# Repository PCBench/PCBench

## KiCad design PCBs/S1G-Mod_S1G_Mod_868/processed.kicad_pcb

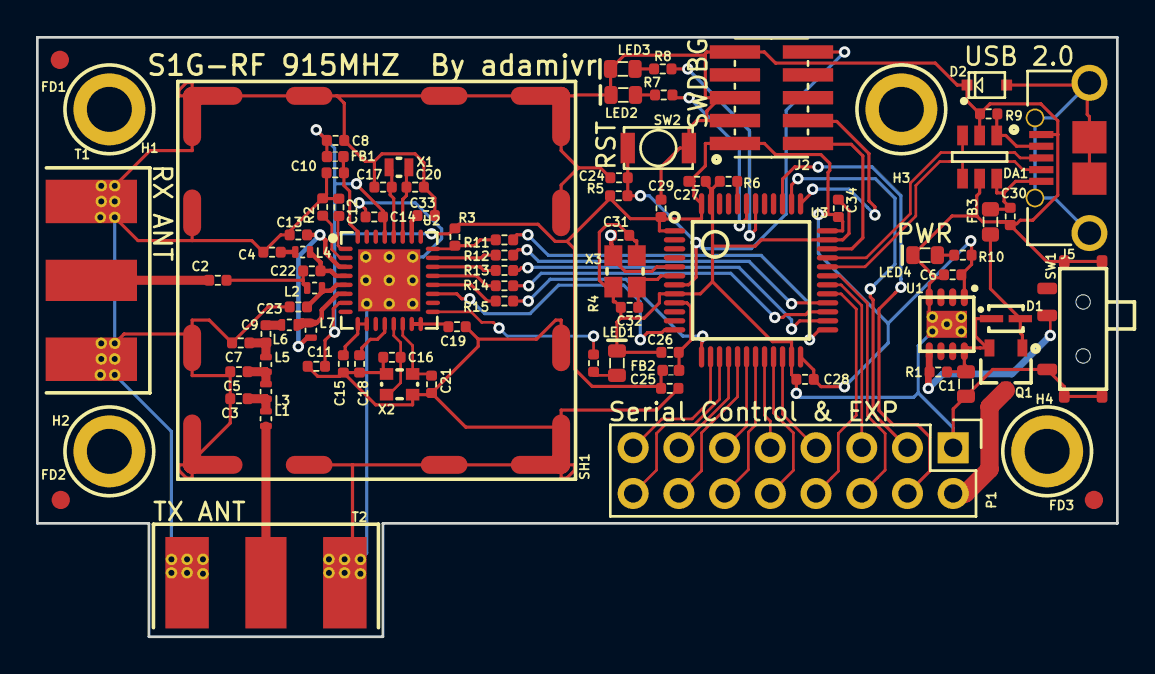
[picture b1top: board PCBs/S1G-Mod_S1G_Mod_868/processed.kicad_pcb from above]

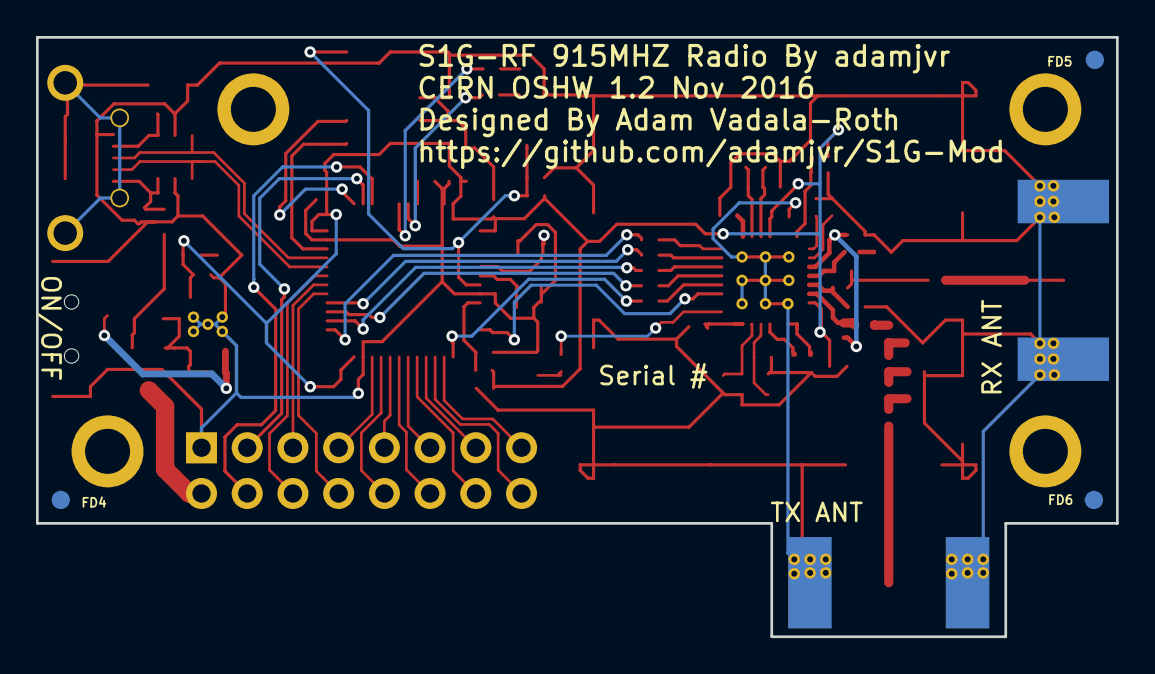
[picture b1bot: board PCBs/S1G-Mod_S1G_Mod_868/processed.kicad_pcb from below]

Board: 4 copper layers, 60.0 x 33.3 mm, 91 parts (3 on the bottom side), 73 nets.

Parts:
C1: CL10A106KQ8NNNC; C0603
C2: CBR04C560F1GAC; C0402
C3, C5: GJM1555C1H2R2WB01D; C0402
C4: GRM1555C1H101GA01D; C0402
C6, C8, C10, C11, C14, C24, C25, C26, C27, C28, C29, C30, C34: CL05B104JP5NNNC; C0402
C7: GJM1555C1H1R0BB01D; C0402
C9: CBR04C470F3GAC; C0402
C12, C13, C15, C19, C33: CL10B224JO8NNNC; C0402
C16, C21, C31, C32: GRM0225C1E8R0WA03L; C0402
C17, C20: CL05C090CB5NNNC; C0402
C18: GRM155R71H152KA01D; C0402
C22: GRM1555C2A2R7CA01D; C0402
C23: GRM1555C1E1R2BA01D; C0402
D1: BAT20JFILM
D2: RSB39VTE-17
DA1: ESDA6V1BC6
FB1, FB2: BLM15HG601SN1D
FB3: MI0603K300R-10
FD1, FD2, FD3, FD4, FD5, FD6: FIDUCIAL
H1, H2, H3, H4: M2.5_Hole; M2.5_HOLE
J2: 20021121-00010C4LF
J5: 0475890001-MicroUSBPort; 0475890001
L1, L2, L5: 0402CS-12NXJL; L0402
L3: 0402CS-24NXJL; L0402
L4: 0402CS-6N2XJL; L0402
L6: 0402CS-1N8XJL; L0402
L7: 0402CS-47NXJL; L0402
LED1, LED2: LTST-C193TBKT-5A; LED0603
LED3: LTST-C191KGKT; LED0603
LED4: LTST-C193KRKT-5A; LED0603
P1: 61301621121
Q1: DMG2307L-7
R1, R3, R6: RC1005F103CS; R0402
R2: ERA-2AEB363X; R0402
R4, R5, R7, R8, R10: RC1005F102CS; R0402
R9: RC1005J473CS; R0402
R11, R12, R13, R14, R15: TNPW0402100RBEED; R0402
SH1: 36103205
SW1: CUS-12TB
SW2: B3U-1000P
T1, T2: 732511150; 0732511150
U1: AP7361-33FGE-7
U2: ADF7023BCPZ
U3: STM32L052C8T6
X1: ABS05-32.768KHZ-9-T
X2: ABM11-140-26.000MHZ-T3
X3: ABM10-166-12.000MHZ-T3

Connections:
+3V3: C6.1, C8.2, C11.1, C14.2, C25.1, C27.1, C28.1, C29.1, C34.1, FB1.1, FB2.1, J2.1, R3.1, R5.1, R10.2, U1.1, U2.7, U2.29, U3.1, U3.24, U3.36, U3.48
/GPIO2: U2.19, U3.12
/MCU - STM32L052K8T6/GPIO_PA8: P1.8, U3.29
/MCU - STM32L052K8T6/GPIO_PA15: P1.3, U3.38
/MCU - STM32L052K8T6/GPIO_PB0: P1.11, U3.18
/MCU - STM32L052K8T6/GPIO_PB1: P1.12, U3.19
/MCU - STM32L052K8T6/GPIO_PB2: P1.9, U3.20
/MCU - STM32L052K8T6/GPIO_PB3: P1.4, U3.39
/MCU - STM32L052K8T6/GPIO_PB10: P1.10, U3.21
/MCU - STM32L052K8T6/GPIO_PB11: P1.7, U3.22
/MCU - STM32L052K8T6/MCU_IRQ: R15.2, U3.13
/MCU - STM32L052K8T6/NRST: C24.1, J2.10, R5.2, SW2.2, U3.7
/MCU - STM32L052K8T6/SPI2_MISO: P1.13, U3.16
/MCU - STM32L052K8T6/SPI2_MOSI: P1.14, U3.17
/MCU - STM32L052K8T6/SPI2_NSS: P1.15, U3.14
/MCU - STM32L052K8T6/SPI2_SCLK: P1.16, U3.15
/MCU - STM32L052K8T6/SPI_CS: R11.2, U3.25
/MCU - STM32L052K8T6/SPI_MISO: R14.2, U3.27
/MCU - STM32L052K8T6/SPI_MOSI: R12.2, U3.28
/MCU - STM32L052K8T6/SPI_SCLK: R13.2, U3.26
/MCU - STM32L052K8T6/SWCLK: J2.4, U3.37
/MCU - STM32L052K8T6/SWDIO: J2.2, U3.34
/MCU - STM32L052K8T6/USART1_RX: P1.6, U3.31
/MCU - STM32L052K8T6/USART1_TX: P1.5, U3.30
/MCU - STM32L052K8T6/USB_DM: DA1.4, J5.2, U3.32
/MCU - STM32L052K8T6/USB_DP: DA1.3, J5.3, U3.33
/MCU_IRQ: R15.1, U2.20
/ON_OFF: R1.1, SW1.2, U1.5
/PSU_IN: P1.2, Q1.3
/SPI_CS: R3.2, R11.1, U2.24
/SPI_MISO: R14.1, U2.21
/SPI_MOSI: R12.1, U2.23
/SPI_SCLK: R13.1, U2.22
/VBUS: D1.1, FB3.1, Q1.1
/VIN: C1.1, D1.2, Q1.2, R1.2, U1.8
/VREF: C10.2, FB1.2, U2.32
GND: C1.2, C3.2, C4.1, C5.2, C6.2, C7.2, C8.1, C10.1, C11.2, C12.1, C13.1, C14.1, C15.2, C16.2, C17.1, C18.2, C19.2, C20.2, C21.2, C23.1, C24.2, C25.2, C26.2, C27.2, C28.2, C29.2, C30.1, C31.2, C32.2, C33.2, C34.2, D2.2, DA1.2, DA1.5, J2.3, J2.5, J2.9, J5.5, LED1.2, LED2.2, LED3.2, LED4.2, P1.1, R2.1, R6.1, R9.2, SH1.1, SW1.1, SW1.4, SW2.1, T1.2, T2.2, U1.4, U1.9, U2.33, U3.8, U3.23, U3.35, U3.47, X2.2, X2.4, X3.2, X3.4
unnamed: C2.1, T1.1
unnamed: C2.2, C22.1, L2.1
unnamed: C3.1, L1.2, L3.1
unnamed: C4.2, L4.1
unnamed: C5.1, L3.2, L5.1
unnamed: C7.1, C9.1, L5.2
unnamed: C9.2, L6.1
unnamed: C12.2, U2.1
unnamed: C13.2, L7.1, U2.3
unnamed: C15.1, U2.9, U2.10
unnamed: C16.1, U2.13, X2.1
unnamed: C17.2, U2.28, X1.1
unnamed: C18.1, U2.12
unnamed: C19.1, U2.15, U2.16
unnamed: C20.1, U2.27, X1.2
unnamed: C21.1, U2.14, X2.3
unnamed: C22.2, L4.2, U2.4
unnamed: C23.2, L2.2, U2.5
unnamed: C26.1, FB2.2, U3.9
unnamed: C30.2, DA1.6, FB3.2, J5.1
unnamed: C31.1, U3.5, X3.1
unnamed: C32.1, U3.6, X3.3
unnamed: C33.1, U2.26
unnamed: D2.1, J5.6, J5.7, J5.8, J5.9, J5.10, J5.11
unnamed: DA1.1, J5.4, R9.1
unnamed: L1.1, T2.1
unnamed: L6.2, L7.2, U2.6
unnamed: LED1.1, R4.2
unnamed: LED2.1, R7.1
unnamed: LED3.1, R8.1
unnamed: LED4.1, R10.1
unnamed: R2.2, U2.2
unnamed: R4.1, U2.17
unnamed: R6.2, U3.44
unnamed: R7.2, U3.43
unnamed: R8.2, U3.42

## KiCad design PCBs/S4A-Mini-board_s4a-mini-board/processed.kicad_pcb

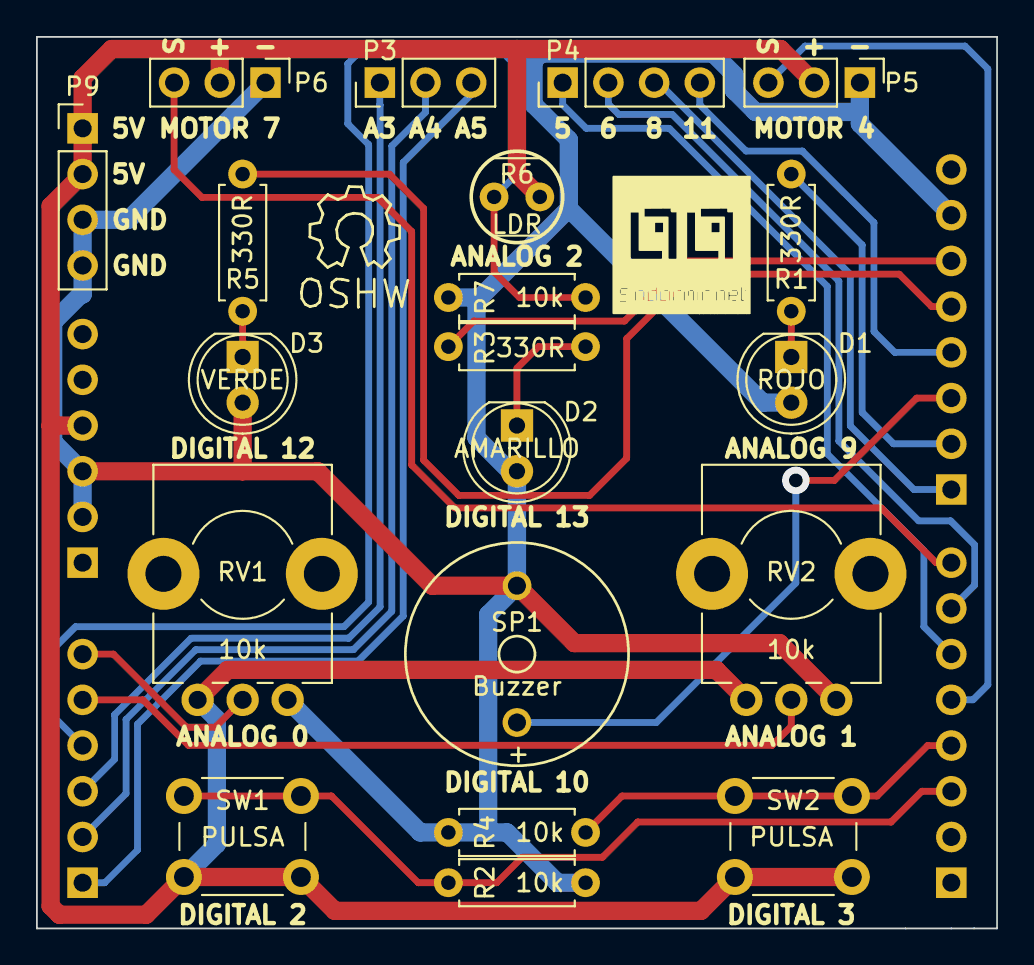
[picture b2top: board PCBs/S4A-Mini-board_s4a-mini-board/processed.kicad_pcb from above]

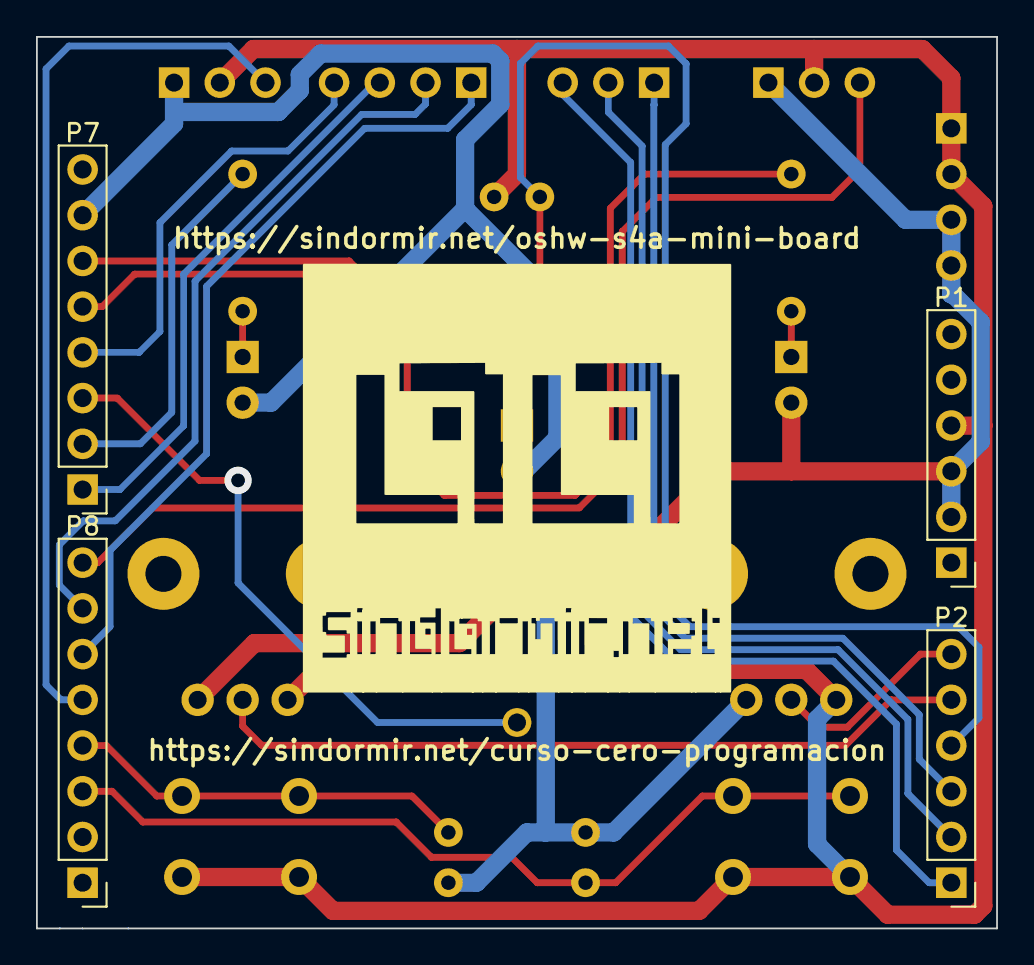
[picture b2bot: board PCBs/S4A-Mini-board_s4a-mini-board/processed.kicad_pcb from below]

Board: 2 copper layers, 53.3 x 49.5 mm, 25 parts (4 on the bottom side), 23 nets.

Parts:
D1: ROJO; LED_D5.0mm
D2: AMARILLO; LED_D5.0mm
D3: VERDE; LED_D5.0mm
P1: Arduino Power header; Pin_Header_Straight_1x06_Pitch2.54mm
P2: Arduino Analog header; Pin_Header_Straight_1x06_Pitch2.54mm
P3: Analog pin; Socket_Strip_Straight_1x03_Pitch2.54mm
P4: Digital pin; Socket_Strip_Straight_1x04_Pitch2.54mm
P5: Servo 1; Pin_Header_Straight_1x03_Pitch2.54mm
P6: Servo 2; Pin_Header_Straight_1x03_Pitch2.54mm
P7: Arduino Digital H header; Pin_Header_Straight_1x08_Pitch2.54mm
P8: Arduino Digital L header; Pin_Header_Straight_1x08_Pitch2.54mm
P9: Power; Socket_Strip_Straight_1x04_Pitch2.54mm
R1, R3, R5: 330R; R_Axial_DIN0207_L6.3mm_D2.5mm_P7.62mm_Horizontal
R2, R4, R7: 10k; R_Axial_DIN0207_L6.3mm_D2.5mm_P7.62mm_Horizontal
R6: LDR; Resistor_LDR_4.9x4.2_RM2.54
RV1, RV2: 10k; Potentiometer_Alps_RK09K_Horizontal
SP1: Buzzer; MagneticBuzzer_ProSignal_ABI-009-RC
SW1, SW2: PULSA; SW_PUSH_6mm_h5mm
Symbol_OSHW-Logo_SilkScreen: VAL**; Symbol_OSHW-Logo_SilkScreen

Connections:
+5V: P1.4, P5.2, P6.2, P9.1, P9.2, R6.1, RV1.3, RV2.3, SW1.1, SW2.1
GND: D1.2, D2.2, D3.2, P1.2, P1.3, P5.1, P6.1, P7.7, P9.3, P9.4, R2.2, R4.2, R7.2, RV1.1, RV2.1, SP1.1
unnamed: D1.1, R1.1
unnamed: D2.1, R3.1
unnamed: D3.1, R5.1
PINA0: P2.6, RV1.2
PINA1: P2.5, RV2.2
PINA2: P2.4, R6.2, R7.1
PINA3: P2.3, P3.1
PINA4: P2.2, P3.2
PINA5: P2.1, P3.3
PIND2: P8.3, R2.1, SW1.2
PIND3: P8.4, R4.1, SW2.2
PIND4: P5.3, P8.5
PIND5: P4.1, P8.6
PIND6: P4.2, P8.7
PIND7: P6.3, P8.8
PIND8: P4.3, P7.1
PIND9: P7.2, R1.2
PIND10: P7.3, SP1.2
PIND11: P4.4, P7.4
PIND12: P7.5, R5.2
PIND13: P7.6, R3.2

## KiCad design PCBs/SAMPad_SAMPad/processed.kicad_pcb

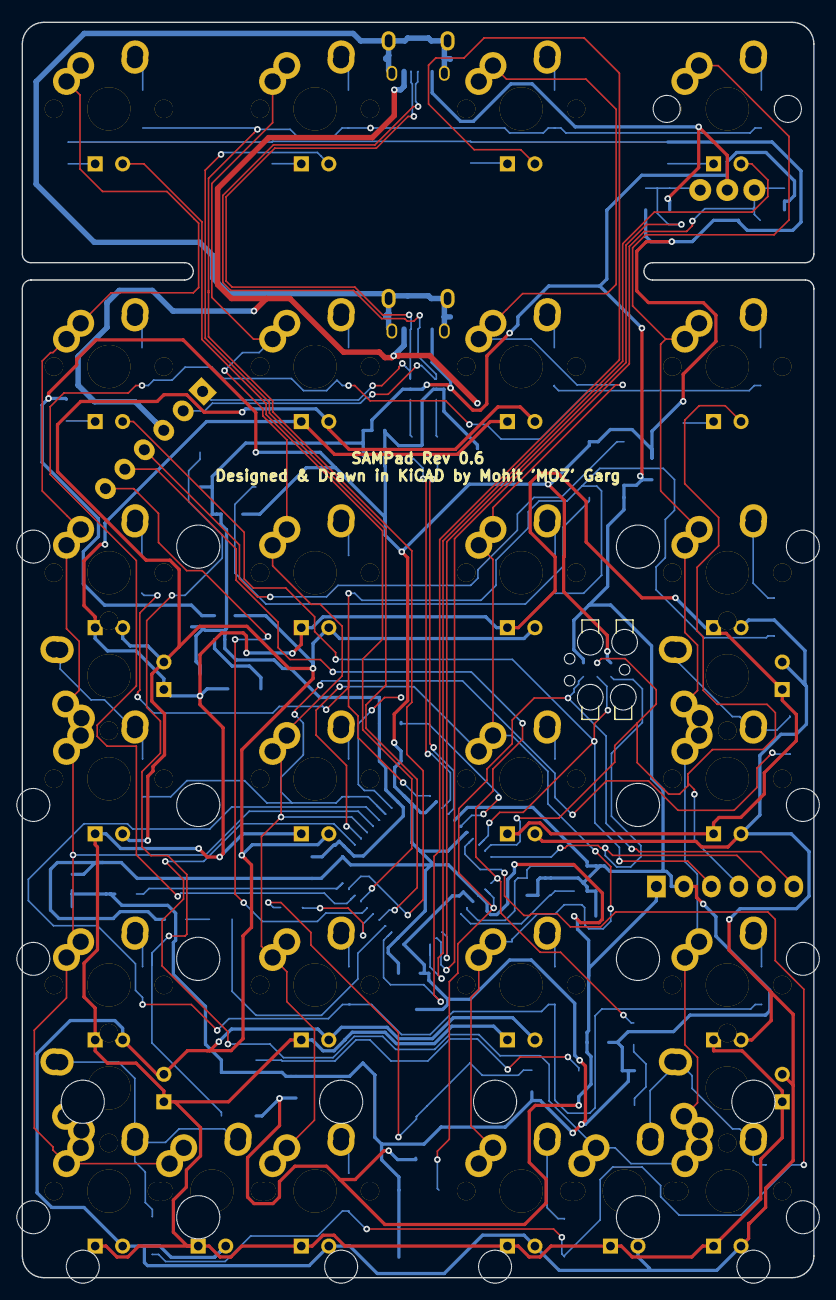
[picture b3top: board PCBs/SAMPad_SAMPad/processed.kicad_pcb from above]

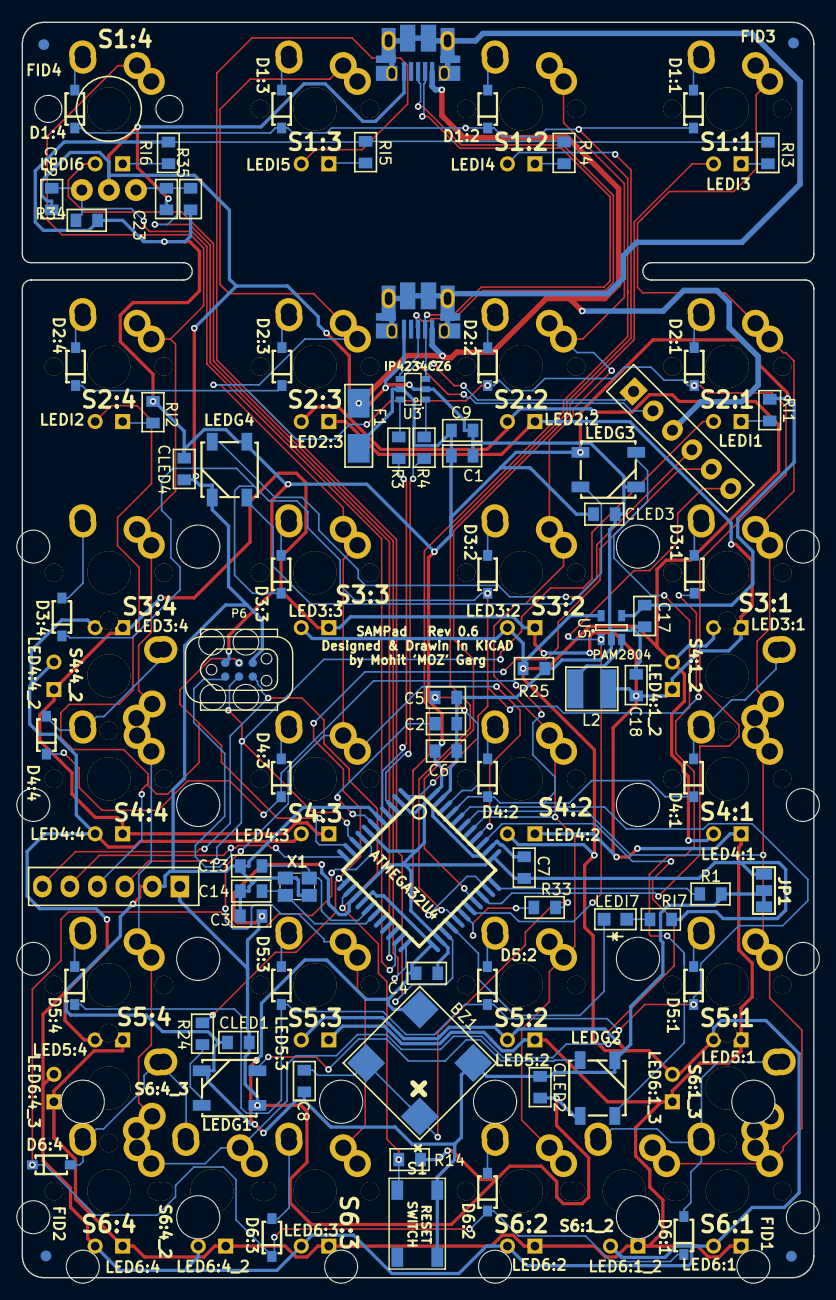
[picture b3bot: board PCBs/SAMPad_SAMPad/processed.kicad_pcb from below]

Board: 2 copper layers, 73.2 x 116.0 mm, 150 parts (83 on the bottom side), 79 nets.

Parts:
BZ1: BUZZER; BUZZER_SMT
C1, C2, C22, C23: 1uF; SMD_0805
C3, C4, C5, C6, C7, C8: 0.1uF; SMD_0805
C9, C17, C18: 10uF; SMD_0805
C13, C14: 8pF; SMD_0805
CLED1, CLED2, CLED3, CLED4: 0.1 uF; SMD_0805
D1:1, D1:2, D1:3, D1:4, D2:1, D2:2, D2:3, D2:4, D3:1, D3:2, D3:3, D3:4, D4:1, D4:2, D4:3, D4:4, D5:1, D5:2, D5:3, D5:4, D6:1, D6:2, D6:3, D6:4: DIODE; SOD123-DIODE
F1: PTC FUSE; Fuse_SMD1206
FID1, FID2, FID3, FID4: MISC; FID
HOLE1: MISC; FID
JP1: JUMPER; JUMPER_SMD_3
L2: 4.7uH; Inductor_Bourn_4mmx4mm
LED2:2, LED2:3, LED3:1, LED3:2, LED3:3, LED3:4, LED4:1, LED4:1_2, LED4:2, LED4:3, LED4:4, LED4:4_2, LED5:1, LED5:2, LED5:3, LED5:4, LED6:1, LED6:1_2, LED6:1_3, LED6:2, LED6:3, LED6:4, LED6:4_2, LED6:4_3: LED; INSW_LEDS_REG
LEDG1, LEDG2, LEDG3, LEDG4: WS2812B
LEDI1, LEDI2, LEDI3, LEDI4, LEDI5, LEDI6: LED; INSW_LEDS_REG
LEDI7: LED; LED_0805
P1, P1_2: USB_CONN; USB_Micro-B
P4, P5: CONN_6; Pin_Header_1x06
P6: ISP6; TC2030_BIG
R1, R34, R35: 10k; SMD_0805
R3, R4: 22; SMD_0805
R14: 100k; SMD_0805
R24: 330; SMD_0805
R25: RLED; SMD_0805
R33: 100; SMD_0805
RI1, RI2, RI3, RI4, RI5, RI6, RI7: 470; SMD_0805
S1: TAC_SWITCH; TACT_5.2x5.2
S1:1, S1:2, S1:3, S1:4, S2:1, S2:2, S2:3, S2:4, S3:1, S3:2, S3:3, S3:4, S4:1, S4:1_2, S4:2, S4:3, S4:4, S4:4_2, S5:1, S5:2, S5:3, S5:4, S6:1, S6:1_2, S6:1_3, S6:2, S6:3, S6:4, S6:4_2, S6:4_3: SW; MXALPS2
S2: ENCODER; ENCODER_12MM
STAB1, STAB2, STAB3, STAB4, STAB5, STAB6: MISC; MX_200
U1: ATMEGA32U4; TQFP44
U3: IP4234CZ6; SOT457
U5: PAM2804; SOT-23-5
X1: CRYSTAL; NX3225SA

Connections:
+5V: C1.1, C3.1, C4.1, C6.1, C7.1, C9.1, C17.1, CLED1.2, CLED2.2, CLED3.1, CLED4.1, F1.2, JP1.1, LEDG1.1, LEDG2.1, LEDG3.1, LEDG4.1, P5.1, P6.2, R14.2, R34.2, R35.1, RI1.2, RI2.2, RI3.2, RI4.2, RI5.2, RI6.2, RI7.2, U1.2, U1.7, U1.14, U1.24, U1.34, U1.44, U3.5, U5.4
/ledmatrix/LEDAN: C18.1, L2.2, LED2:2.1, LED2:3.1, LED3:1.1, LED3:2.1, LED3:3.1, LED3:4.1, LED4:1.1, LED4:1_2.1, LED4:2.1, LED4:3.1, LED4:4.1, LED4:4_2.1, LED5:1.1, LED5:2.1, LED5:3.1, LED5:4.1, LED6:1.1, LED6:1_2.1, LED6:1_3.1, LED6:2.1, LED6:3.1, LED6:4.1, LED6:4_2.1, LED6:4_3.1
/ledmatrix/LEDCATH: LED2:2.2, LED2:3.2, LED3:1.2, LED3:2.2, LED3:3.2, LED3:4.2, LED4:1.2, LED4:1_2.2, LED4:2.2, LED4:3.2, LED4:4.2, LED4:4_2.2, LED5:1.2, LED5:2.2, LED5:3.2, LED5:4.2, LED6:1.2, LED6:1_2.2, LED6:1_3.2, LED6:2.2, LED6:3.2, LED6:4.2, LED6:4_2.2, LED6:4_3.2, R25.2, U5.5
/ledmatrix/LEDI1: LEDI1.2, P5.3, P6.3, U1.9
/ledmatrix/LEDI2: LEDI2.2, P5.4, P6.4, U1.10
/ledmatrix/LEDI3: LEDI3.2, U1.30
/ledmatrix/LEDI4: LEDI4.2, U1.27
/ledmatrix/LEDI5: LEDI5.2, U1.25
/ledmatrix/LEDI6: LEDI6.2, U1.22
/ledmatrix/LEDI7: LEDI7.2, U1.26
/ledmatrix/RGBDIN: P4.5, R24.2, U1.12
/ledmatrix/RGBDOUT: LEDG4.2, P4.4
/mcu/BUZZER: R33.1, U1.28
/mcu/COL1: S1:1.1, S2:1.1, S3:1.1, S4:1.1, S4:1_2.1, S5:1.1, S6:1.1, S6:1_2.1, S6:1_3.1, U1.39
/mcu/COL2: S1:2.1, S2:2.1, S3:2.1, S4:2.1, S5:2.1, S6:2.1, U1.38
/mcu/COL3: S1:3.1, S2:3.1, S3:3.1, S4:3.1, S5:3.1, S6:3.1, U1.37
/mcu/COL4: S1:4.1, S2:4.1, S3:4.1, S4:4.1, S4:4_2.1, S5:4.1, S6:4.1, S6:4_2.1, S6:4_3.1, U1.36
/mcu/D+: P1.3, P1_2.3, P4.2, U3.4
/mcu/D-: P1.2, P1_2.2, P4.1, U3.3
/mcu/ENCA: C22.1, R34.1, S2.1, U1.21
/mcu/ENCB: C23.1, R35.2, S2.3, U1.20
/mcu/HWBE: R1.2, U1.33
/mcu/LEDBL: P4.6, U1.29, U5.1
/mcu/MCURST: P5.6, P6.5, R14.1, S1.2, U1.13
/mcu/MISO: P5.5, P6.1, U1.11
/mcu/ROW1: D1:1.2, D1:2.2, D1:3.2, D1:4.2, U1.32
/mcu/ROW2: D2:1.2, D2:2.2, D2:3.2, D2:4.2, U1.31
/mcu/ROW3: D3:1.2, D3:2.2, D3:3.2, D3:4.2, U1.1
/mcu/ROW4: D4:1.2, D4:2.2, D4:3.2, D4:4.2, U1.41
/mcu/ROW5: D5:1.2, D5:2.2, D5:3.2, D5:4.2, U1.40
/mcu/ROW6: D6:1.2, D6:2.2, D6:3.2, D6:4.2, U1.8
/mcu/SHDGND: P1.6, P1_2.6
/mcu/USB_D+: R3.2, U1.4
/mcu/USB_D-: R4.2, U1.3
/mcu/VUSB: F1.1, P1.1, P1_2.1, P4.3
/mcu/XTAL1: C14.1, U1.17, X1.3
/mcu/XTAL2: C13.1, U1.16, X1.1
unnamed: BZ1.1, C8.2, R33.2
unnamed: C2.1, U1.6
unnamed: C5.1, U1.42
unnamed: D1:1.1, S1:1.2
unnamed: D1:2.1, S1:2.2
unnamed: D1:3.1, S1:3.2
unnamed: D1:4.1, S1:4.2
unnamed: D2:1.1, S2:1.2
unnamed: D2:2.1, S2:2.2
unnamed: D2:3.1, S2:3.2
unnamed: D2:4.1, S2:4.2
unnamed: D3:1.1, S3:1.2
unnamed: D3:2.1, S3:2.2
unnamed: D3:3.1, S3:3.2
unnamed: D3:4.1, S3:4.2
unnamed: D4:1.1, S4:1.2, S4:1_2.2
unnamed: D4:2.1, S4:2.2
unnamed: D4:3.1, S4:3.2
unnamed: D4:4.1, S4:4.2, S4:4_2.2
unnamed: D5:1.1, S5:1.2
unnamed: D5:2.1, S5:2.2
unnamed: D5:3.1, S5:3.2
unnamed: D5:4.1, S5:4.2
unnamed: D6:1.1, S6:1.2, S6:1_2.2, S6:1_3.2
unnamed: D6:2.1, S6:2.2
unnamed: D6:3.1, S6:3.2
unnamed: D6:4.1, S6:4.2, S6:4_2.2, S6:4_3.2
unnamed: L2.1, U5.3
unnamed: LEDG1.2, LEDG2.4
unnamed: LEDG1.4, R24.1
unnamed: LEDG2.2, LEDG3.4
unnamed: LEDG3.2, LEDG4.4
unnamed: LEDI1.1, RI1.1
unnamed: LEDI2.1, RI2.1
unnamed: LEDI3.1, RI3.1
unnamed: LEDI4.1, RI4.1
unnamed: LEDI5.1, RI5.1
unnamed: LEDI6.1, RI6.1
unnamed: LEDI7.1, RI7.1
unnamed: R3.1, U3.6
unnamed: R4.1, U3.1
VSS: BZ1.2, C1.2, C2.2, C3.2, C4.2, C5.2, C6.2, C7.2, C8.1, C9.2, C13.2, C14.2, C17.2, C18.2, C22.2, C23.2, CLED1.1, CLED2.1, CLED3.2, CLED4.2, JP1.2, JP1.3, LEDG1.3, LEDG2.3, LEDG3.3, LEDG4.3, P1.5, P1_2.5, P5.2, P6.6, R1.1, R25.1, S1.3, S1.4, S2.2, U1.5, U1.15, U1.23, U1.35, U1.43, U3.2, U5.2, X1.2, X1.4

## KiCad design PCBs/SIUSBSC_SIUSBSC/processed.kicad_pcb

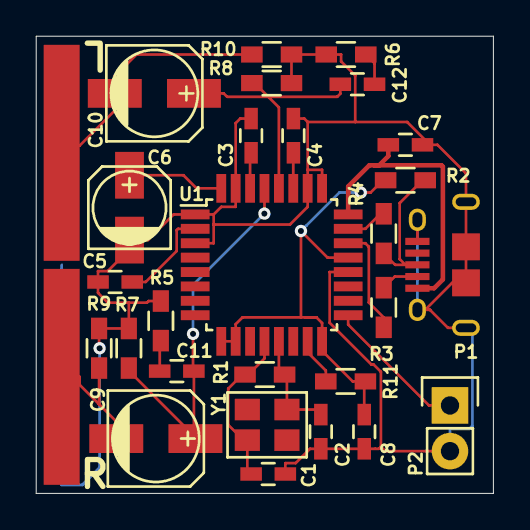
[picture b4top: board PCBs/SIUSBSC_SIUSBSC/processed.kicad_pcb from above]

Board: 2 copper layers, 25.4 x 25.4 mm, 30 parts (1 on the bottom side), 21 nets.

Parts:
C1, C2: 18pF; C_0603_HandSoldering
C3, C4, C5, C7, C8: 1uF; C_0603_HandSoldering
C6: 10uF; c_elec_4x5.3
C9, C10: 100uF; c_elec_5x5.3
C11, C12: 0.022uF; C_0603_HandSoldering
P1: USB_MICRO_B; CONN_USB_MICRO_B_FCI_10118194
P2: I2S; Pin_Header_Straight_1x02
P3: RIGHT; PAD_12.00x2.00mm
P4: LEFT; PAD_12.00x2.00mm
P5: GND; PAD_24.00x2.00mm
R1: 1M; R_0603_HandSoldering
R2, R11: 1K5; R_0603_HandSoldering
R3, R4: 22R; R_0603_HandSoldering
R5, R6: 16R; R_0603_HandSoldering
R7, R8, R9, R10: 3K3; R_0603_HandSoldering
U1: PCM2706; TQFP-32_7x7mm_Pitch0.8mm
Y1: 12MHz; XTAL_SMD_3225

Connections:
/D+: R4.2, U1.23
/D-: R3.2, U1.22
/DOUT: P2.1, U1.17
/DT: R11.1, U1.15
/FOUTL: C10.2, P4.1, R10.1
/FOUTR: C9.2, P3.1, R9.1
/USB_D+: P1.3, R2.2, R4.1
/USB_D-: P1.2, R3.1
/VBUS: C7.2, P1.1, U1.24
/VCCL: C4.1, U1.27
/VCCP: C5.2, U1.2
/VCCR: C3.1, U1.30
/VCOM: C6.1, U1.32
/VOUTL: C10.1, C12.1, R8.1, U1.28
/VOUTR: C9.1, C11.1, R7.1, U1.29
/XTI: C1.1, R1.2, U1.12, Y1.1
/XTO: C2.1, R1.1, U1.13, Y1.3
GND: C1.2, C2.2, C3.2, C4.2, C5.1, C6.2, C7.1, C8.2, P1.5, P1.6, P2.2, P5.1, R5.2, R6.2, R7.2, R8.2, R9.2, R10.2, U1.1, U1.3, U1.20, U1.25, U1.26, U1.31
unnamed: C11.2, R5.1
unnamed: C12.2, R6.1
VDD: C8.1, R2.1, R11.2, U1.9, U1.10, U1.16, U1.21

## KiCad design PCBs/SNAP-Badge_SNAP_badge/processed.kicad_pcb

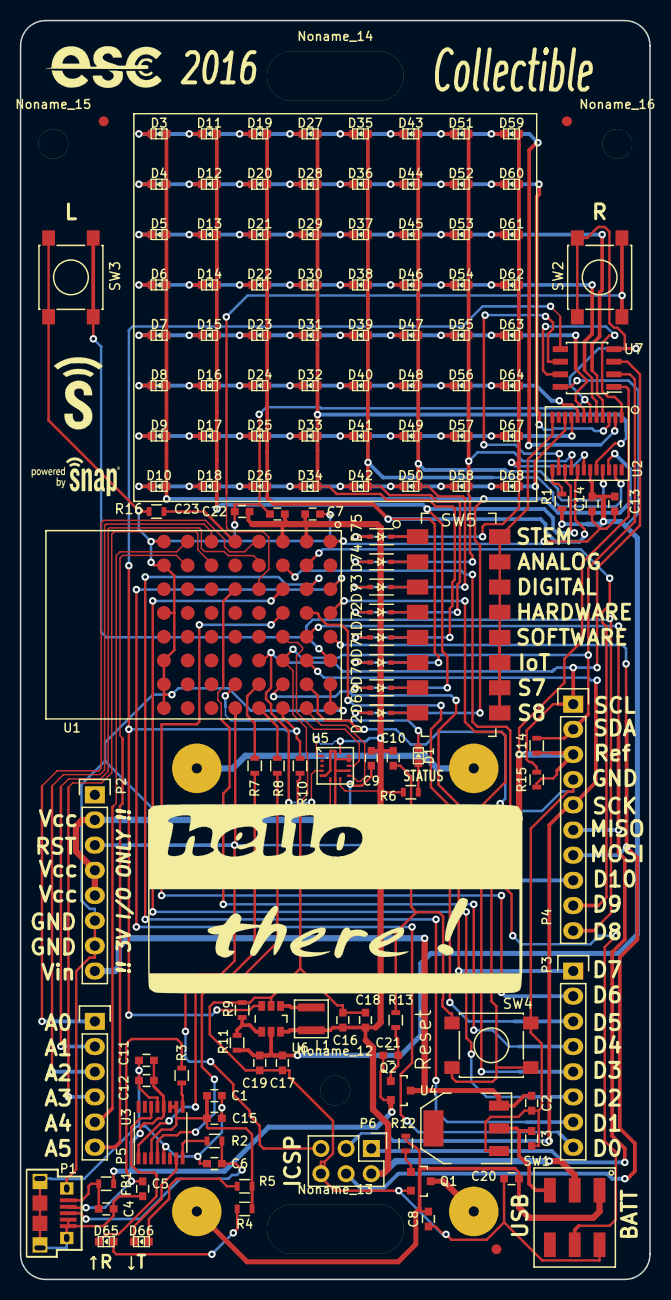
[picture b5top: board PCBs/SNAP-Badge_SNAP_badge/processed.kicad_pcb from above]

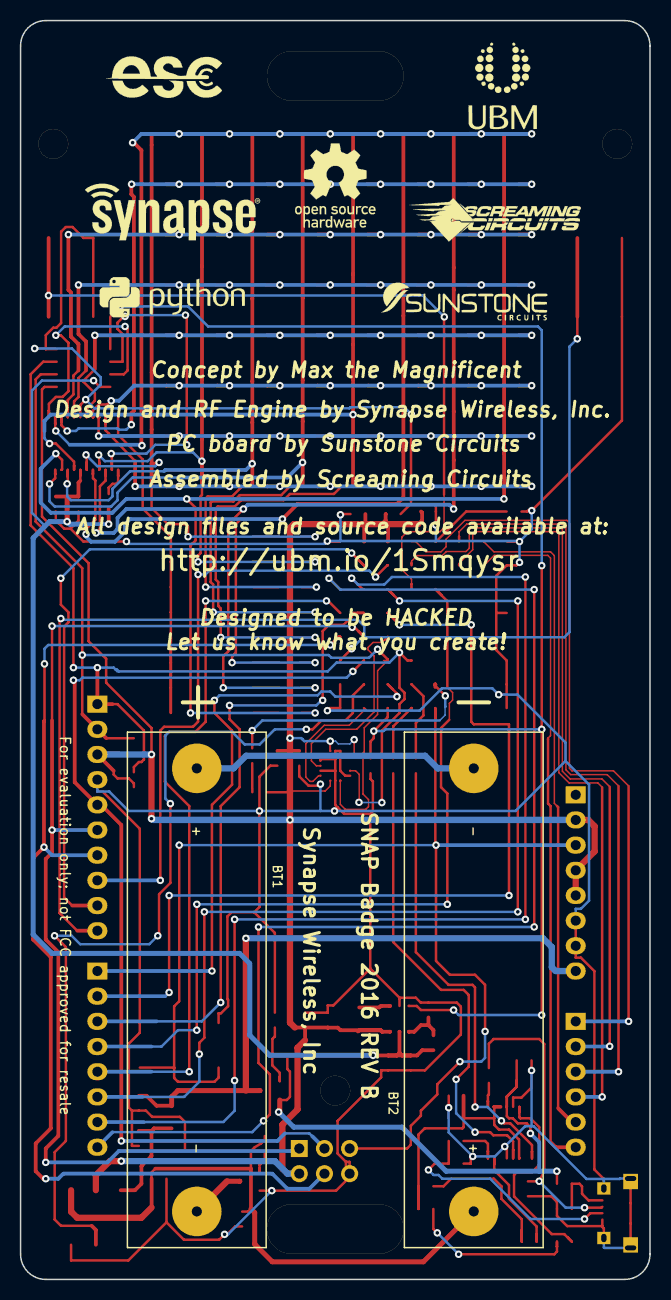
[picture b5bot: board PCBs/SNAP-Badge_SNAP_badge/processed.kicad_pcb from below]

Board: 2 copper layers, 63.5 x 127.0 mm, 157 parts (9 on the bottom side), 86 nets.

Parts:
BT1, BT2: 1.5V; BATT_2466
C1, C2, C10, C12, C14, C18, C20, C21: 0.1uF; C_0603
C3, C16: 10uF; C_0603
C4: 10nF; C_0603
C5, C6: 47pF; C_0603
C7, C8, C22, C23: 22uF; C_0603
C9, C11, C13, C15, C17, C19: 4.7uF; C_0603
D1, D3, D4, D5, D6, D7, D8, D9, D10, D11, D12, D13, D14, D15, D16, D17, D18, D19, D20, D21, D22, D23, D24, D25, D26, D27, D28, D29, D30, D31, D32, D33, D34, D35, D36, D37, D38, D39, D40, D41, D42, D43, D44, D45, D46, D47, D48, D49, D50, D51, D52, D53, D54, D55, D56, D57, D58, D59, D60, D61, D62, D63, D64, D65, D66, D67, D68: LED; Led_0603
D2, D69, D70, D71, D72, D73, D74, D75: 1N4148W; SOD-323
FB1: 600 OHM 500MA; R_0603
Fiducial_Mark: VAL**; Fiducial_Mark
Fiducial_Mark_2, Fiducial_Mark_3: VAL**; Fiducial_Mark
L1: 4.7uH 0.9A; TYS-2
Noname_1: LOGO; Hello
Noname_2: LOGO; UBM_logo
Noname_3: LOGO; Sunstone_logo
Noname_4: LOGO; Screaming_logo
Noname_5: LOGO; Synapse_logo
Noname_6: LOGO; Python_logo
Noname_7: OSHW_logo
Noname_8, Noname_11: ESC_logo
Noname_9: syn_logo1_8x8
Noname_10: pb_snap
Noname_12, Noname_15, Noname_16: MountingHole_3mm
Noname_13, Noname_14: LanyardSlot
P1: MicroB; USBmicroB
P2, P3: CONN_01X08; Socket_Strip_Straight_1x08
P4: CONN_01X10; Socket_Strip_Straight_1x10
P5: CONN_01X06; Socket_Strip_Straight_1x06
P6: CONN_02X03; Pin_Header_Straight_2x03
Q1: ZXMN2F30FHCT-ND; SOT-23
Q2: Si2305DS; SOT-23
R1: 10k; R_0603
R2, R3: 27; R_0603
R4, R5, R6: 270; R_0603
R7, R8: 1k; R_0603
R9: 200k; R_0603
R10, R12: 100k; R_0603
R11: 1M; R_0603
R13: 39k; R_0603
R14, R15, R16: 4.7k; R_0603
SW1: SWITCH_DPDT; SO-DPDT-6
SW2, SW3, SW4: SW_PUSH; SW_SPST_PTS645
SW5: SW_DIP_8; DIPSW-16
U1: SM220
U2: AS1115; QSOP-24
U3: FT230XS; SSOP-16_3.9x4.9mm_Pitch0.635mm
U4: LD1117S33CTR; SOT-223
U5: LIS3DH; LGA16_3x3
U6: TPS61070; TSOT-6-MK06A
U7: NLSX4373; SOIC-8_3.9x4.9mm_Pitch1.27mm

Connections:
/*IS_USB: SW1.5, U1.G2
/*RESET: P2.3, P6.5, SW4.2, U1.H5
/ACC_INT1: U1.E3, U5.11
/ACC_INT2: U1.H2, U5.9
/BTN_LFT: P4.10, SW3.2, U1.F1
/BTN_RT: SW2.2, U1.C4
/LED_matrix/DIG0: D3.1, D11.1, D19.1, D27.1, D35.1, D43.1, D51.1, D59.1, U2.2
/LED_matrix/DIG1: D4.1, D12.1, D20.1, D28.1, D36.1, D44.1, D52.1, D60.1, U2.3
/LED_matrix/DIG2: D5.1, D13.1, D21.1, D29.1, D37.1, D45.1, D53.1, D61.1, U2.4
/LED_matrix/DIG3: D6.1, D14.1, D22.1, D30.1, D38.1, D46.1, D54.1, D62.1, U2.5
/LED_matrix/DIG4: D7.1, D15.1, D23.1, D31.1, D39.1, D47.1, D55.1, D63.1, U2.7
/LED_matrix/DIG5: D8.1, D16.1, D24.1, D32.1, D40.1, D48.1, D56.1, D64.1, U2.8
/LED_matrix/DIG6: D9.1, D17.1, D25.1, D33.1, D41.1, D49.1, D57.1, D67.1, U2.9
/LED_matrix/DIG7: D10.1, D18.1, D26.1, D34.1, D42.1, D50.1, D58.1, D68.1, U2.10
/LED_matrix/LED_3V: C13.1, C14.1, C17.1, C19.1, R1.1, R11.1, U2.19, U6.5, U7.8
/LED_matrix/LED_SCL: U2.14, U7.6
/LED_matrix/LED_SDA: U2.1, U7.7
/LED_matrix/SEGA: D11.2, D12.2, D13.2, D14.2, D15.2, D16.2, D17.2, D18.2, D69.2, U2.15
/LED_matrix/SEGB: D19.2, D20.2, D21.2, D22.2, D23.2, D24.2, D25.2, D26.2, D70.2, U2.17
/LED_matrix/SEGC: D27.2, D28.2, D29.2, D30.2, D31.2, D32.2, D33.2, D34.2, D71.2, U2.20
/LED_matrix/SEGD: D35.2, D36.2, D37.2, D38.2, D39.2, D40.2, D41.2, D42.2, D72.2, U2.23
/LED_matrix/SEGDP: D2.2, D3.2, D4.2, D5.2, D6.2, D7.2, D8.2, D9.2, D10.2, U2.22
/LED_matrix/SEGE: D43.2, D44.2, D45.2, D46.2, D47.2, D48.2, D49.2, D50.2, D73.2, U2.21
/LED_matrix/SEGF: D51.2, D52.2, D53.2, D54.2, D55.2, D56.2, D57.2, D58.2, D74.2, U2.16
/LED_matrix/SEGG: D59.2, D60.2, D61.2, D62.2, D63.2, D64.2, D67.2, D68.2, D75.2, U2.18
/MISO: P4.6, P6.1, U1.E2
/MOSI: P4.7, P6.4, U1.E1
/PB5: P3.5, U1.D1
/PB6: P3.3, U1.D2
/PB7: P3.2, U1.D3
/PD4: P3.1, U1.G3
/PE0: P3.8, U1.C1
/PE1: P3.7, U1.C2
/PE3: P4.9, U1.B2
/PE4: P3.6, U1.C3
/PE5: P4.8, U1.B3
/PE7: P3.4, U1.C5
/PF0: P5.1, U1.A4
/PF1: P5.2, U1.B4
/PF4: P5.3, U1.A6
/PF5: P5.4, U1.B6
/PF6: P5.5, U1.A7
/PF7: P5.6, U1.B7
/RXLED: D66.1, U3.7
/SCLK: P4.5, P6.3, U1.F2
/STATUS_LED: D1.1, U1.G5
/TXLED: D65.1, U3.14
/USB_RXD: R8.2, U1.H4
/USB_TXD: R7.2, U1.G4
/VIN_USB: C11.1, C12.1, C21.1, FB1.2, Q2.2, U3.12
/VREG_IN: C2.1, P2.8, Q2.3, U4.3
GND: C1.2, C2.2, C3.2, C4.2, C5.2, C6.2, C7.2, C8.2, C9.2, C10.2, C11.2, C12.2, C13.2, C14.2, C15.2, C16.2, C17.2, C18.2, C19.2, C20.2, C22.2, C23.2, P1.4, P1.5, P1.6, P2.6, P2.7, P4.4, P6.6, Q1.2, R9.1, R10.1, R13.1, R16.2, SW1.6, SW2.1, SW3.1, SW4.1, U1.A1, U1.A8, U1.B8, U1.D8, U1.F8, U1.G1, U1.G8, U1.H1, U1.H8, U2.6, U3.5, U3.13, U4.1, U5.5, U5.7, U5.10, U5.12, U5.13, U5.15, U5.16, U6.2, U7.4
I2C_SCL: P4.1, R15.2, U1.F4, U5.4, U7.3
I2C_SDA: P4.2, R14.2, U1.F3, U5.6, U7.2
LED_PWR_EN: R10.2, U1.H3, U6.3, U7.5
unnamed: BT1.1, BT2.2
unnamed: BT1.2, Q1.3
unnamed: BT2.1, C8.1, C20.1, R12.1, SW1.1
unnamed: C1.1, C15.1, R4.1, R5.1, U3.3, U3.10, U3.11
unnamed: C3.1, SW1.3, U4.2
unnamed: C4.1, FB1.1, P1.1
unnamed: C5.1, P1.2, R3.2
unnamed: C6.1, P1.3, R2.2
unnamed: C21.2, Q2.1, R13.2
unnamed: D1.2, R6.2
unnamed: D2.1, SW5.8
unnamed: D65.2, R4.2
unnamed: D66.2, R5.2
unnamed: D69.1, SW5.7
unnamed: D70.1, SW5.6
unnamed: D71.1, SW5.5
unnamed: D72.1, SW5.4
unnamed: D73.1, SW5.3
unnamed: D74.1, SW5.2
unnamed: D75.1, SW5.1
unnamed: L1.1, U6.1
unnamed: Q1.1, R12.2
unnamed: R1.2, U2.13
unnamed: R2.1, U3.8
unnamed: R3.1, U3.9
unnamed: R7.1, U3.1
unnamed: R8.1, U3.4
unnamed: R9.2, R11.2, U6.4
unnamed: R16.1, U1.A5
unnamed: SW5.9, SW5.10, SW5.11, SW5.12, SW5.13, SW5.14, SW5.15, SW5.16, U2.12
VCC: C7.1, C9.1, C10.1, C16.1, C18.1, C22.1, C23.1, L1.2, P2.2, P2.4, P2.5, P4.3, P6.2, R6.1, R14.1, R15.1, SW1.2, U1.A2, U1.A3, U5.1, U5.8, U5.14, U6.6, U7.1

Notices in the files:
PCBs/S4A-Mini-board_s4a-mini-board/processed.kicad_pcb:
Copyright (C) 2015-2017 sindormir.net
Released under GNU/GPL 3 License https://www.gnu.org/licenses/gpl.html
